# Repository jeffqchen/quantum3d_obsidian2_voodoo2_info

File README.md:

# Quantum3D Obsidian2 Arcade Voodoo2 Info

I have luckily obtained TWO Quantum3D Obsidian2 arcade Voodoo2 cards from a kind eBay seller. They were both broken, so I spend a few weeks investigating and fixing them up, plus designing upgrades to enhance its functionalities. I hope my work will help some of you repair and make your Q3D cards work better.

## Add-on Projects

I have designed the following mods for this card.
- VGA Input Board
- U21 Xilinx CPLD Replacement
- SLI Bridge. Both rigid & ribbon type
- Protective Armor

### VGA Input Board

The Q3D arcade card does not come with a VGA input like a retail Voodoo 2 card. However, it has a pin header footprint on the PCB for that purpose.

I have designed a PCB to plug into the pin header, so you can add a VGA male port, plug in the VGA output of your 2D video card via that Voodoo passthrough cable.

### U21 Xilinx CPLD Replacement

The U21 chip, a Xilinx CPLD, controls mainly sync signals that's output to the VGA output.

There seems to be a few situations wit this chip.
- Some arcade boards come with a security setup and this chip won't function as-is.
- Sometimes this Xilinx chip dies, and you won't have any video output on the screen.

Both situations will render the card useless. I designed a simple logic circuit to function similarly to the unlocked Xilinx CPLD.

### SLI Bridge

This card can do SLI! However you need to add in a few missing components before that. With that part taken care of, I've come up with a rigid SLI bridge board that helps you SLI two of these same cards, or with a reference card. The info on how to create a ribbon type cable will also be available.

### Protective Armor

This set of 3D printed armor will protect sensitive SMD components and improve handling of the card, while making the card look way more nicer. It wouldn't hurt to try!

## Mods

Solder on 2MB of EDO RAM chips to the FBI on the back of the card to make it a 12MB Voodoo 2.

Restore picture brightness to the full PC standard.

All information is available in the [Project Wiki](https://github.com/jeffqchen/quantum3d_obsidian2_voodoo2_info/wiki) pages.

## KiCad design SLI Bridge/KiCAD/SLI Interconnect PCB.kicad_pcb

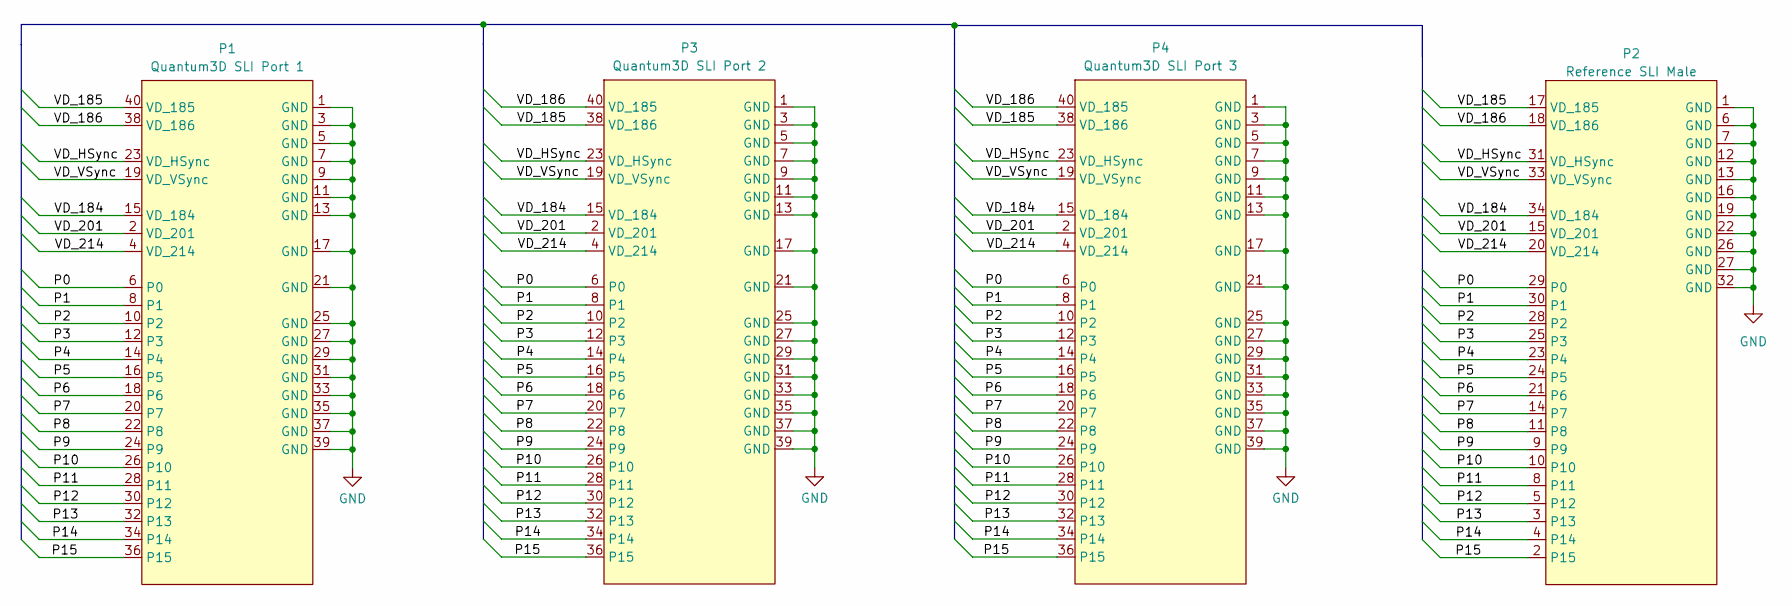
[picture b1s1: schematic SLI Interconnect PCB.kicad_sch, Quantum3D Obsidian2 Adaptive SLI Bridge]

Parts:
P1: Quantum3D SLI Port 1; Quantum3D_SLI_JP2_Female
P2: Reference SLI Male; Reference_SLI_Male
P3: Quantum3D SLI Port 2; Quantum3D_SLI_JP2_Female
P4: Quantum3D SLI Port 3; Quantum3D_SLI_JP2_Female

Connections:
/P0: P1.6 (P0), P2.29 (P0), P3.6 (P0), P4.6 (P0)
/P1: P1.8 (P1), P2.30 (P1), P3.8 (P1), P4.8 (P1)
/P2: P1.10 (P2), P2.28 (P2), P3.10 (P2), P4.10 (P2)
/P3: P1.12 (P3), P2.25 (P3), P3.12 (P3), P4.12 (P3)
/P4: P1.14 (P4), P2.23 (P4), P3.14 (P4), P4.14 (P4)
/P5: P1.16 (P5), P2.24 (P5), P3.16 (P5), P4.16 (P5)
/P6: P1.18 (P6), P2.21 (P6), P3.18 (P6), P4.18 (P6)
/P7: P1.20 (P7), P2.14 (P7), P3.20 (P7), P4.20 (P7)
/P8: P1.22 (P8), P2.11 (P8), P3.22 (P8), P4.22 (P8)
/P9: P1.24 (P9), P2.9, P3.24 (P9), P4.24 (P9)
/P10: P1.26 (P10), P2.10, P3.26 (P10), P4.26 (P10)
/P11: P1.28 (P11), P2.8 (P11), P3.28 (P11), P4.28 (P11)
/P12: P1.30 (P12), P2.5 (P12), P3.30 (P12), P4.30 (P12)
/P13: P1.32 (P13), P2.3 (P13), P3.32 (P13), P4.32 (P13)
/P14: P1.34 (P14), P2.4 (P14), P3.34 (P14), P4.34 (P14)
/P15: P1.36 (P15), P2.2 (P15), P3.36 (P15), P4.36 (P15)
/VD_184: P1.15 (VD_184), P2.34 (VD_184), P3.15 (VD_184), P4.15 (VD_184)
/VD_185: P1.40 (VD_185), P2.17 (VD_185), P3.38 (VD_186), P4.38 (VD_186)
/VD_186: P1.38 (VD_186), P2.18 (VD_186), P3.40 (VD_185), P4.40 (VD_185)
/VD_201: P1.2 (VD_201), P2.15 (VD_201), P3.2 (VD_201), P4.2 (VD_201)
/VD_214: P1.4 (VD_214), P2.20 (VD_214), P3.4 (VD_214), P4.4 (VD_214)
/VD_HSync: P1.23 (VD_HSync), P2.31 (VD_HSync), P3.23 (VD_HSync), P4.23 (VD_HSync)
/VD_VSync: P1.19 (VD_VSync), P2.33 (VD_VSync), P3.19 (VD_VSync), P4.19 (VD_VSync)
GND: P1.1 (GND), P1.3 (GND), P1.5 (GND), P1.7 (GND), P1.9 (GND), P1.11 (GND), P1.13 (GND), P1.17 (GND), P1.21 (GND), P1.25 (GND), P1.27 (GND), P1.29 (GND), P1.31 (GND), P1.33 (GND), P1.35 (GND), P1.37 (GND), P1.39 (GND), P2.1 (GND), P2.6 (GND), P2.7 (GND), P2.12 (GND), P2.13 (GND), P2.16 (GND), P2.19 (GND), P2.22 (GND), P2.26 (GND), P2.27 (GND), P2.32 (GND), P3.1 (GND), P3.3 (GND), P3.5 (GND), P3.7 (GND), P3.9 (GND), P3.11 (GND), P3.13 (GND), P3.17 (GND), P3.21 (GND), P3.25 (GND), P3.27 (GND), P3.29 (GND), P3.31 (GND), P3.33 (GND), P3.35 (GND), P3.37 (GND), P3.39 (GND), P4.1 (GND), P4.3 (GND), P4.5 (GND), P4.7 (GND), P4.9 (GND), P4.11 (GND), P4.13 (GND), P4.17 (GND), P4.21 (GND), P4.25 (GND), P4.27 (GND), P4.29 (GND), P4.31 (GND), P4.33 (GND), P4.35 (GND), P4.37 (GND), P4.39 (GND)

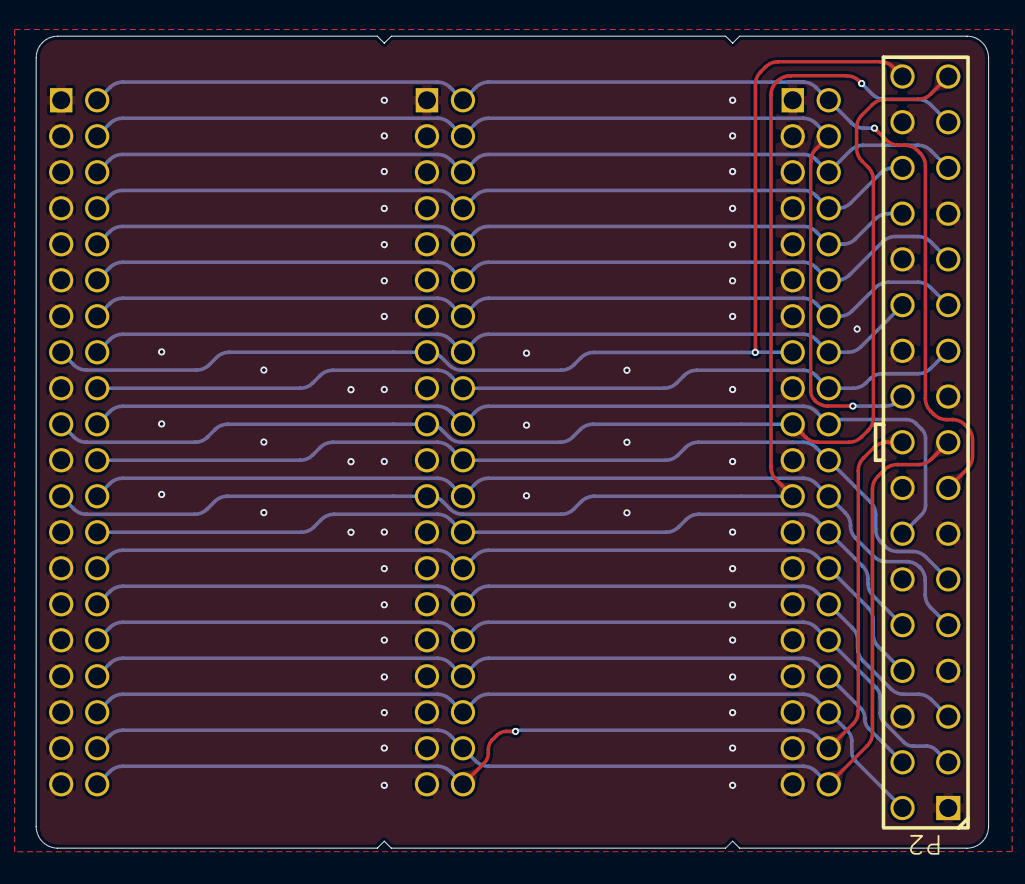
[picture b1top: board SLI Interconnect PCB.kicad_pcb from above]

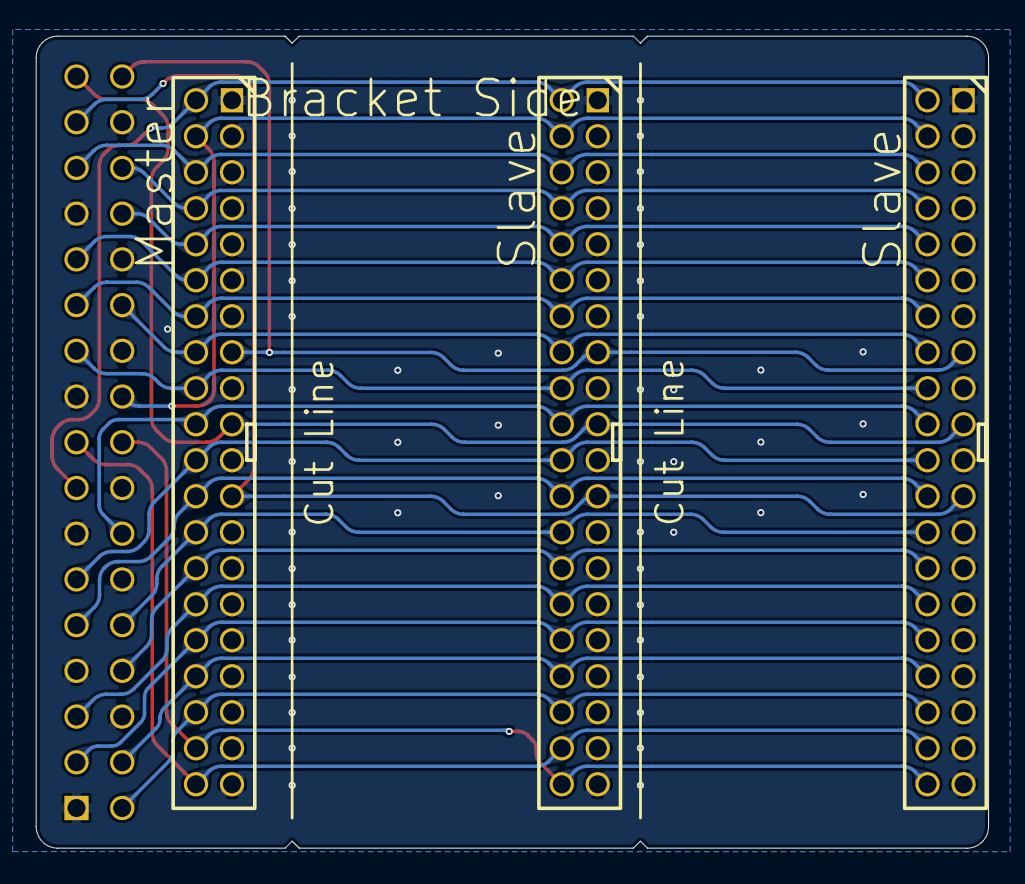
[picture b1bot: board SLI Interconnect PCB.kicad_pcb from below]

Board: 2 copper layers, 52.9 x 45.1 mm, 4 parts (3 on the bottom side), 24 nets.

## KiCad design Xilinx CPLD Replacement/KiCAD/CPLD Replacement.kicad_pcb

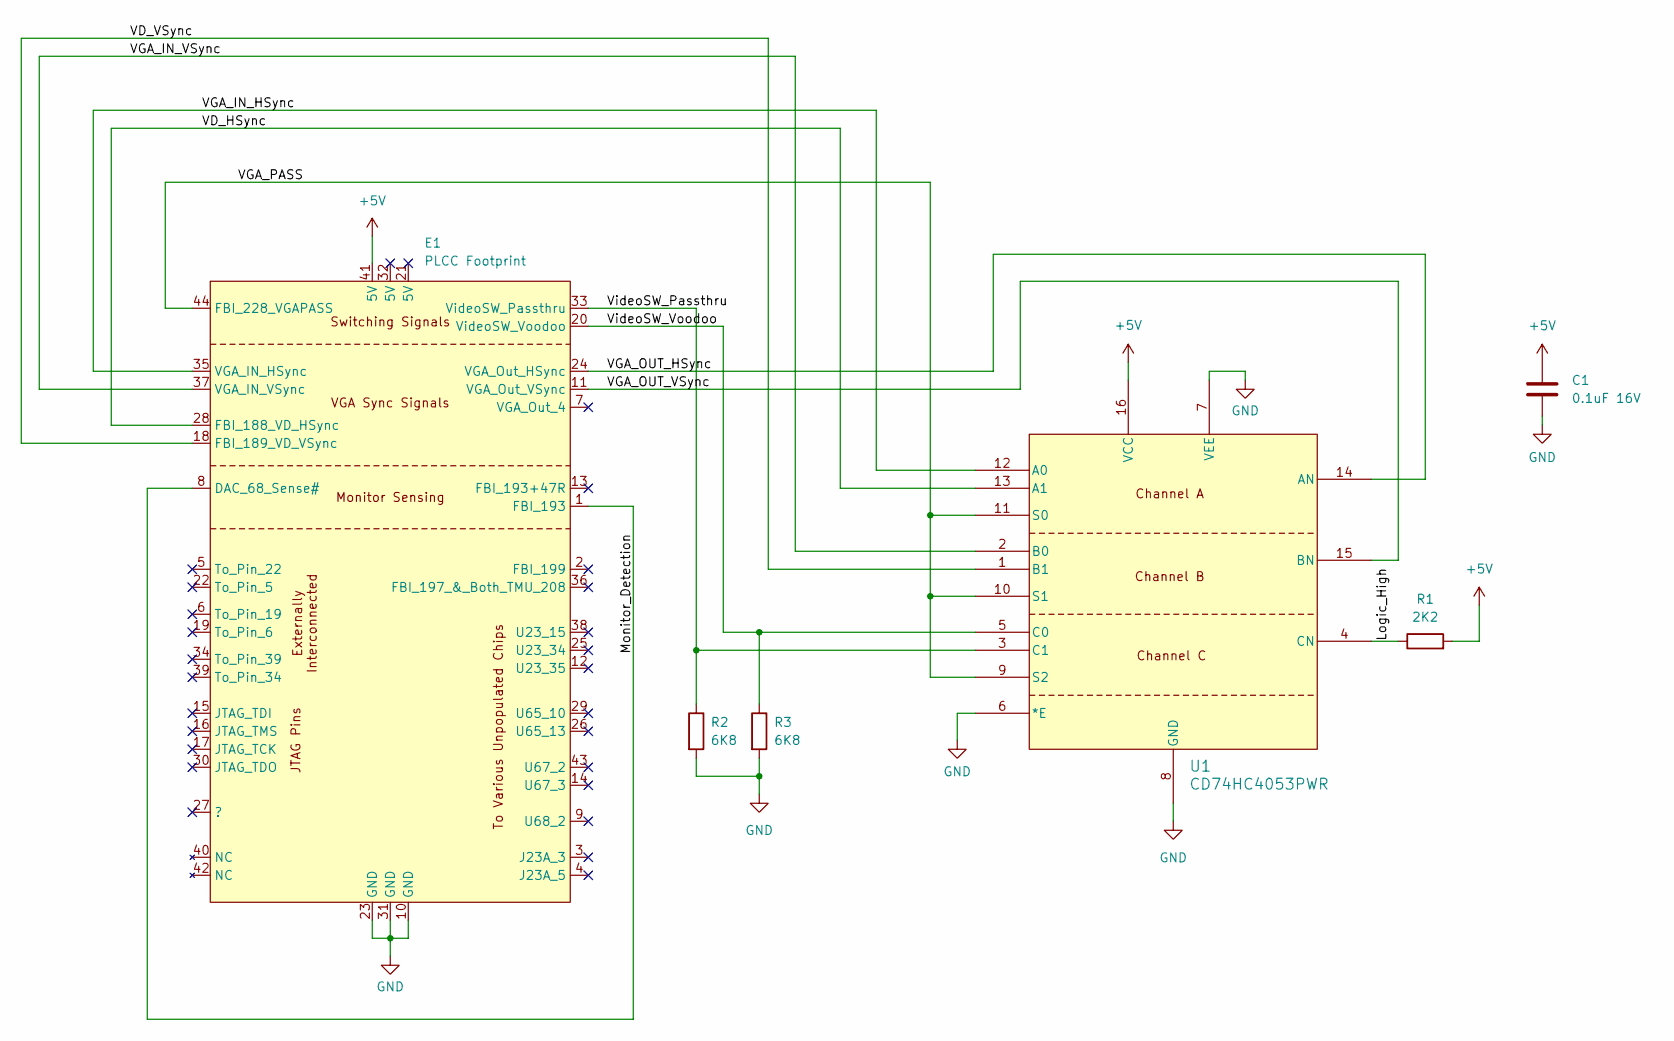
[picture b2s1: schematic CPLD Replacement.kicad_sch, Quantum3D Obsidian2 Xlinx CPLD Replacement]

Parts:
C1: 0.1uF 16V; R_0603_1608Metric_Pad0.98x0.95mm_HandSolder
E1: PLCC Footprint; CPLD_Replacement_44
R1: 2K2; R_0603_1608Metric_Pad0.98x0.95mm_HandSolder
R2, R3: 6K8; R_0603_1608Metric_Pad0.98x0.95mm_HandSolder
U1: CD74HC4053PWR; PW16

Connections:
+5V: C1.1, E1.41 (5V), R1.2, U1.16 (VCC)
/Logic_High: R1.1, U1.4 (CN)
/Monitor_Detection: E1.1 (FBI_193), E1.8 (DAC_68_Sense#)
/VD_HSync: E1.28 (FBI_188_VD_HSync), U1.13 (A1)
/VD_VSync: E1.18 (FBI_189_VD_VSync), U1.1 (B1)
/VGA_IN_HSync: E1.35 (VGA_IN_HSync), U1.12 (A0)
/VGA_IN_VSync: E1.37 (VGA_IN_VSync), U1.2 (B0)
/VGA_OUT_HSync: E1.24 (VGA_Out_HSync), U1.14 (AN)
/VGA_OUT_VSync: E1.11 (VGA_Out_VSync), U1.15 (BN)
/VGA_PASS: E1.44 (FBI_228_VGAPASS), U1.9 (S2), U1.10 (S1), U1.11 (S0)
/VideoSW_Passthru: E1.33 (VideoSW_Passthru), R2.1, U1.3 (C1)
/VideoSW_Voodoo: E1.20 (VideoSW_Voodoo), R3.1, U1.5 (C0)
GND: C1.2, E1.10 (GND), E1.23 (GND), E1.31 (GND), R2.2, R3.2, U1.6 (*E), U1.7 (VEE), U1.8 (GND)

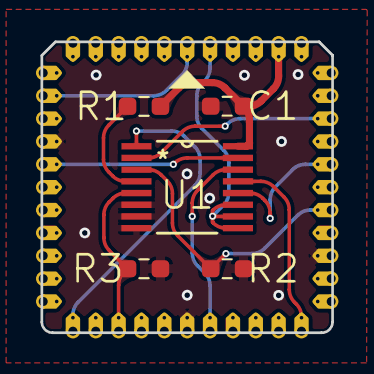
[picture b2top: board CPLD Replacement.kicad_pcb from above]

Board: 2 copper layers, 16.2 x 16.2 mm, 6 parts (0 on the bottom side), 13 nets.

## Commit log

2024-11-07 KiCAD Projects & 3D Print Files
2024-11-07 Update KiCAD Files
2024-11-18 Upload armor
